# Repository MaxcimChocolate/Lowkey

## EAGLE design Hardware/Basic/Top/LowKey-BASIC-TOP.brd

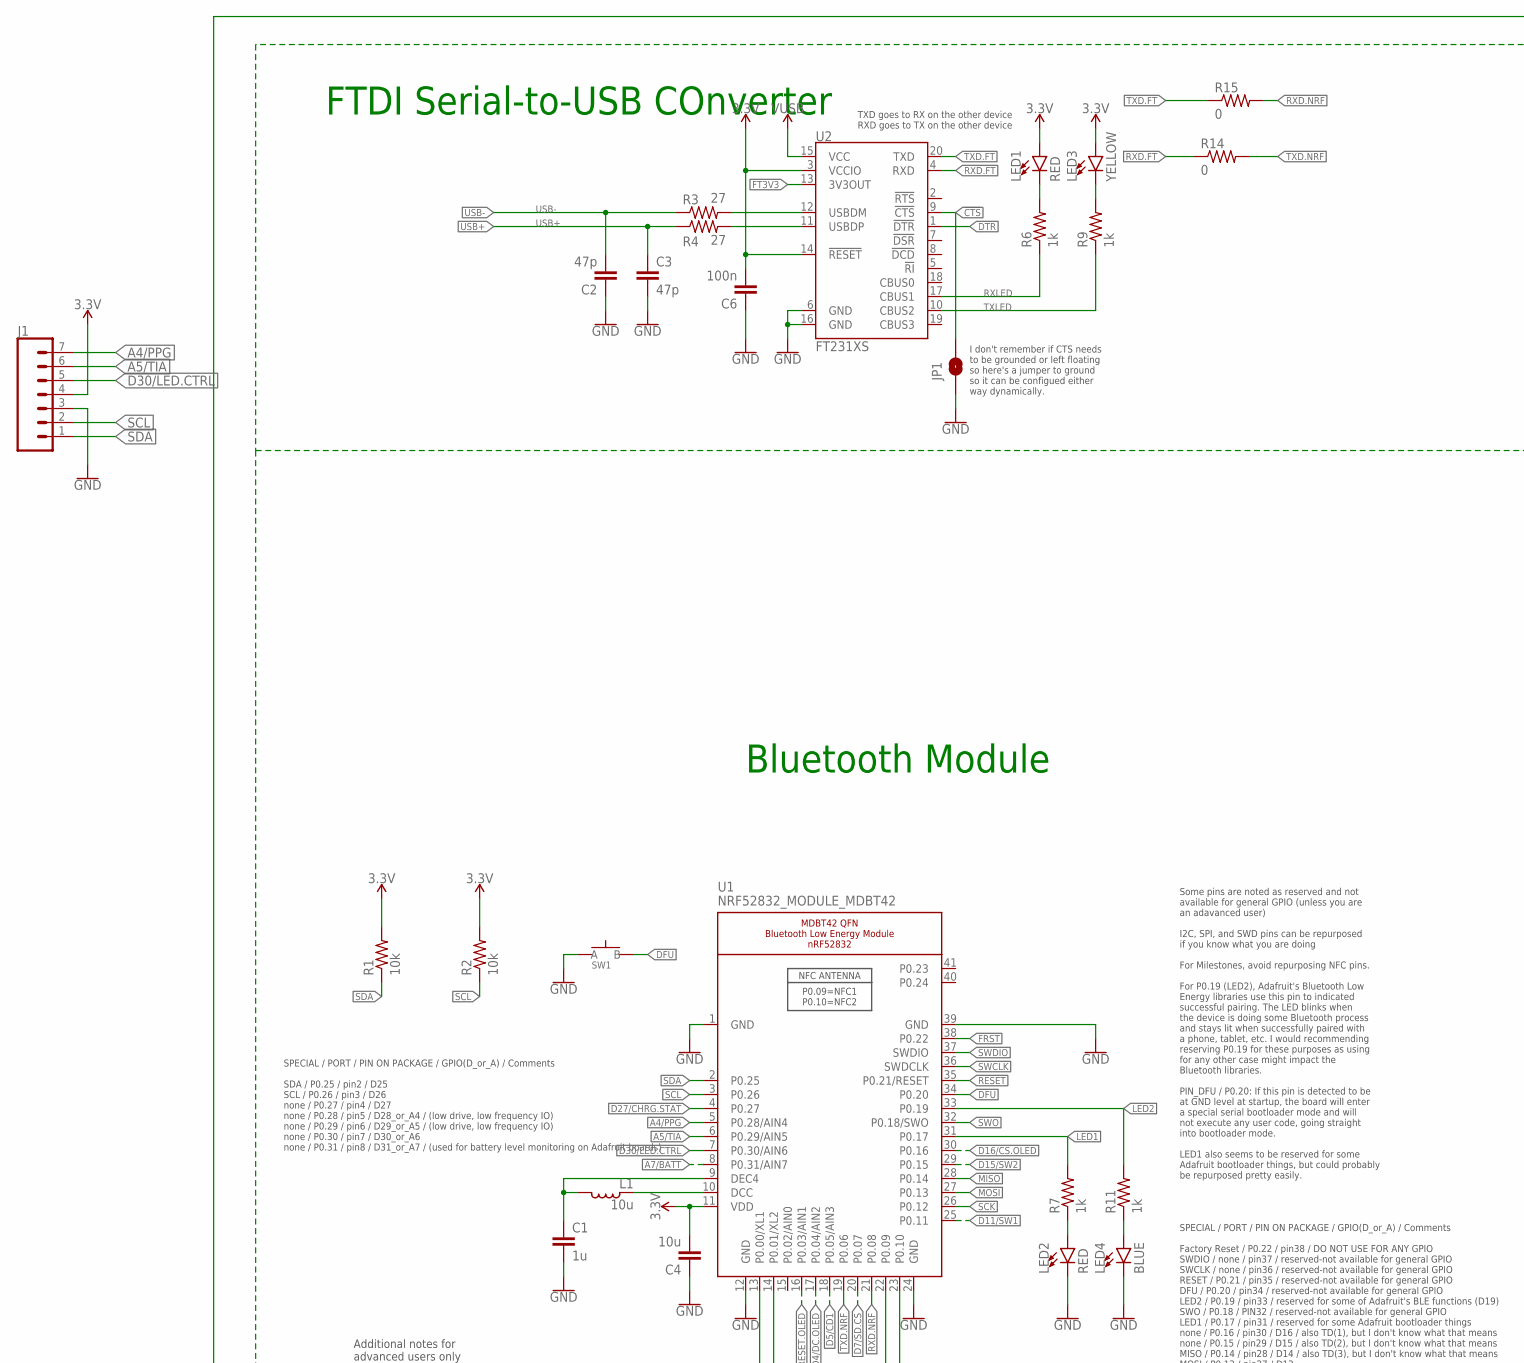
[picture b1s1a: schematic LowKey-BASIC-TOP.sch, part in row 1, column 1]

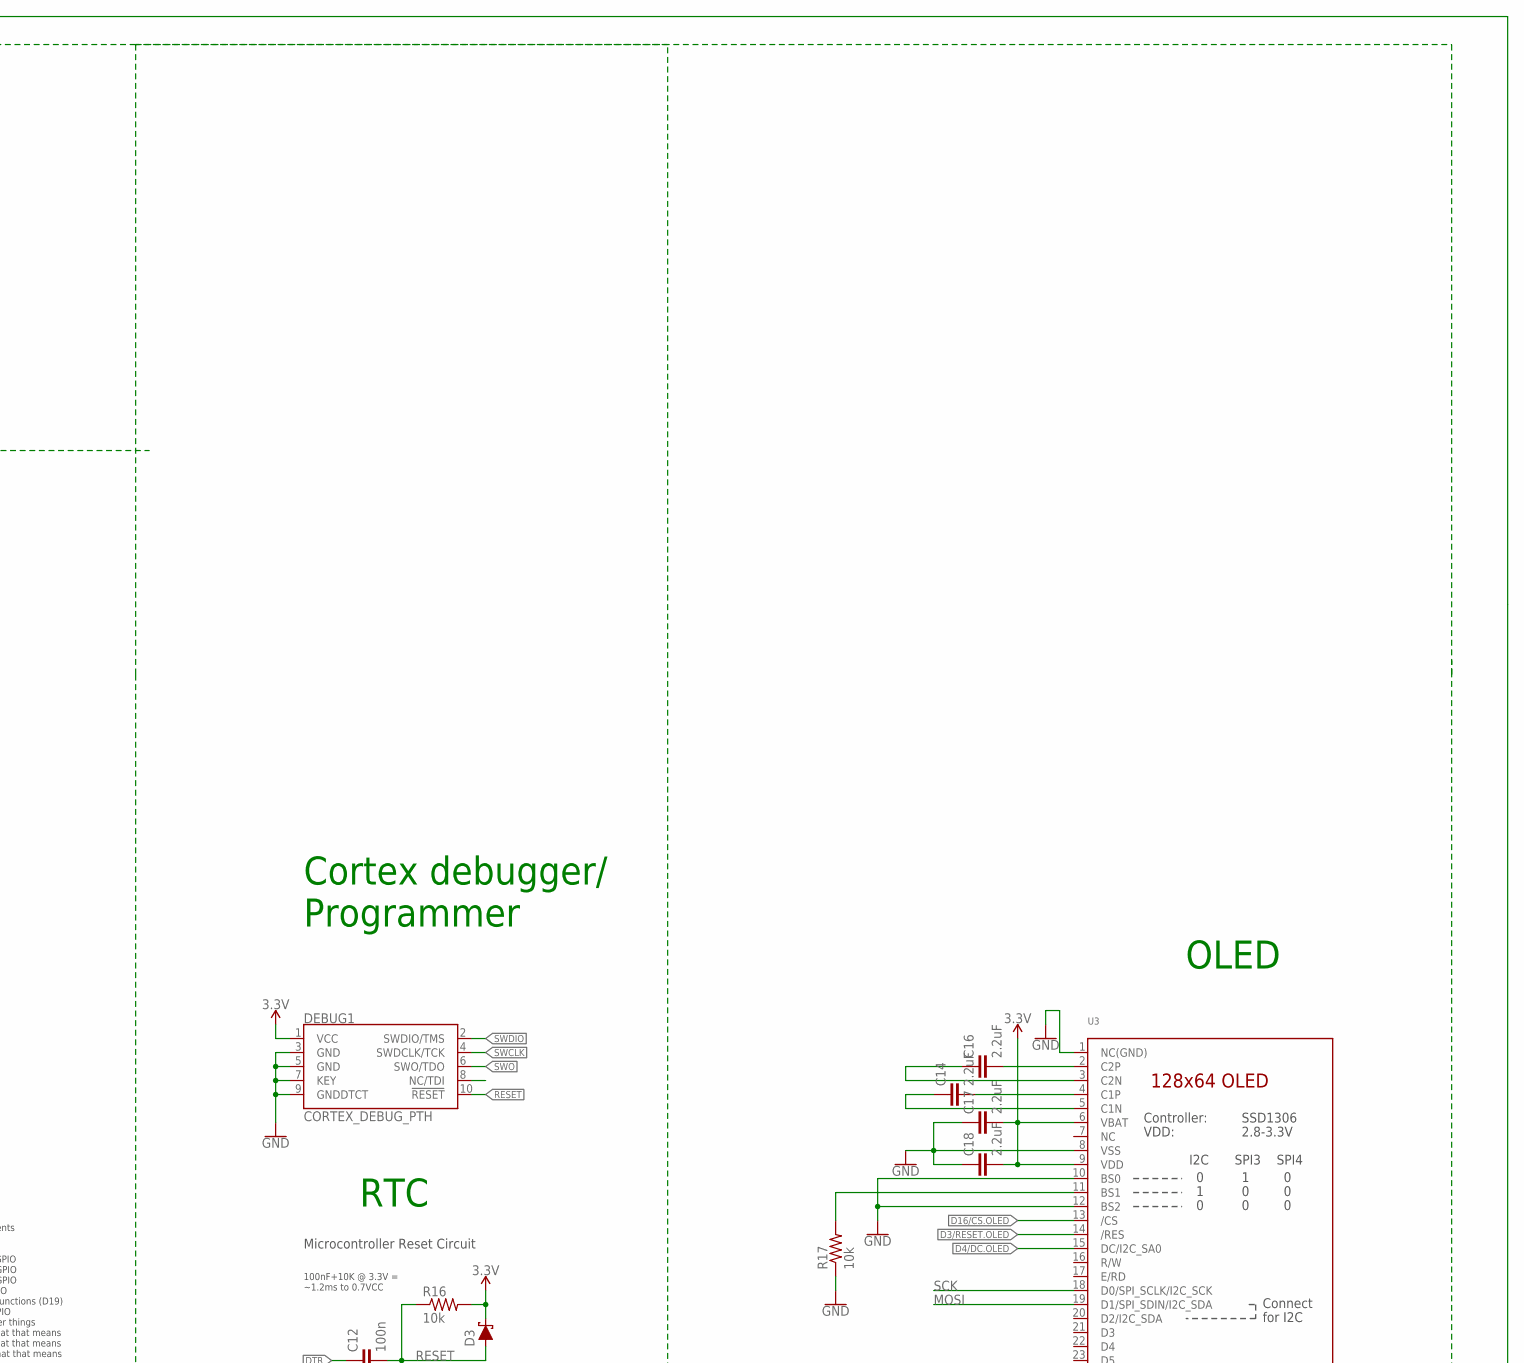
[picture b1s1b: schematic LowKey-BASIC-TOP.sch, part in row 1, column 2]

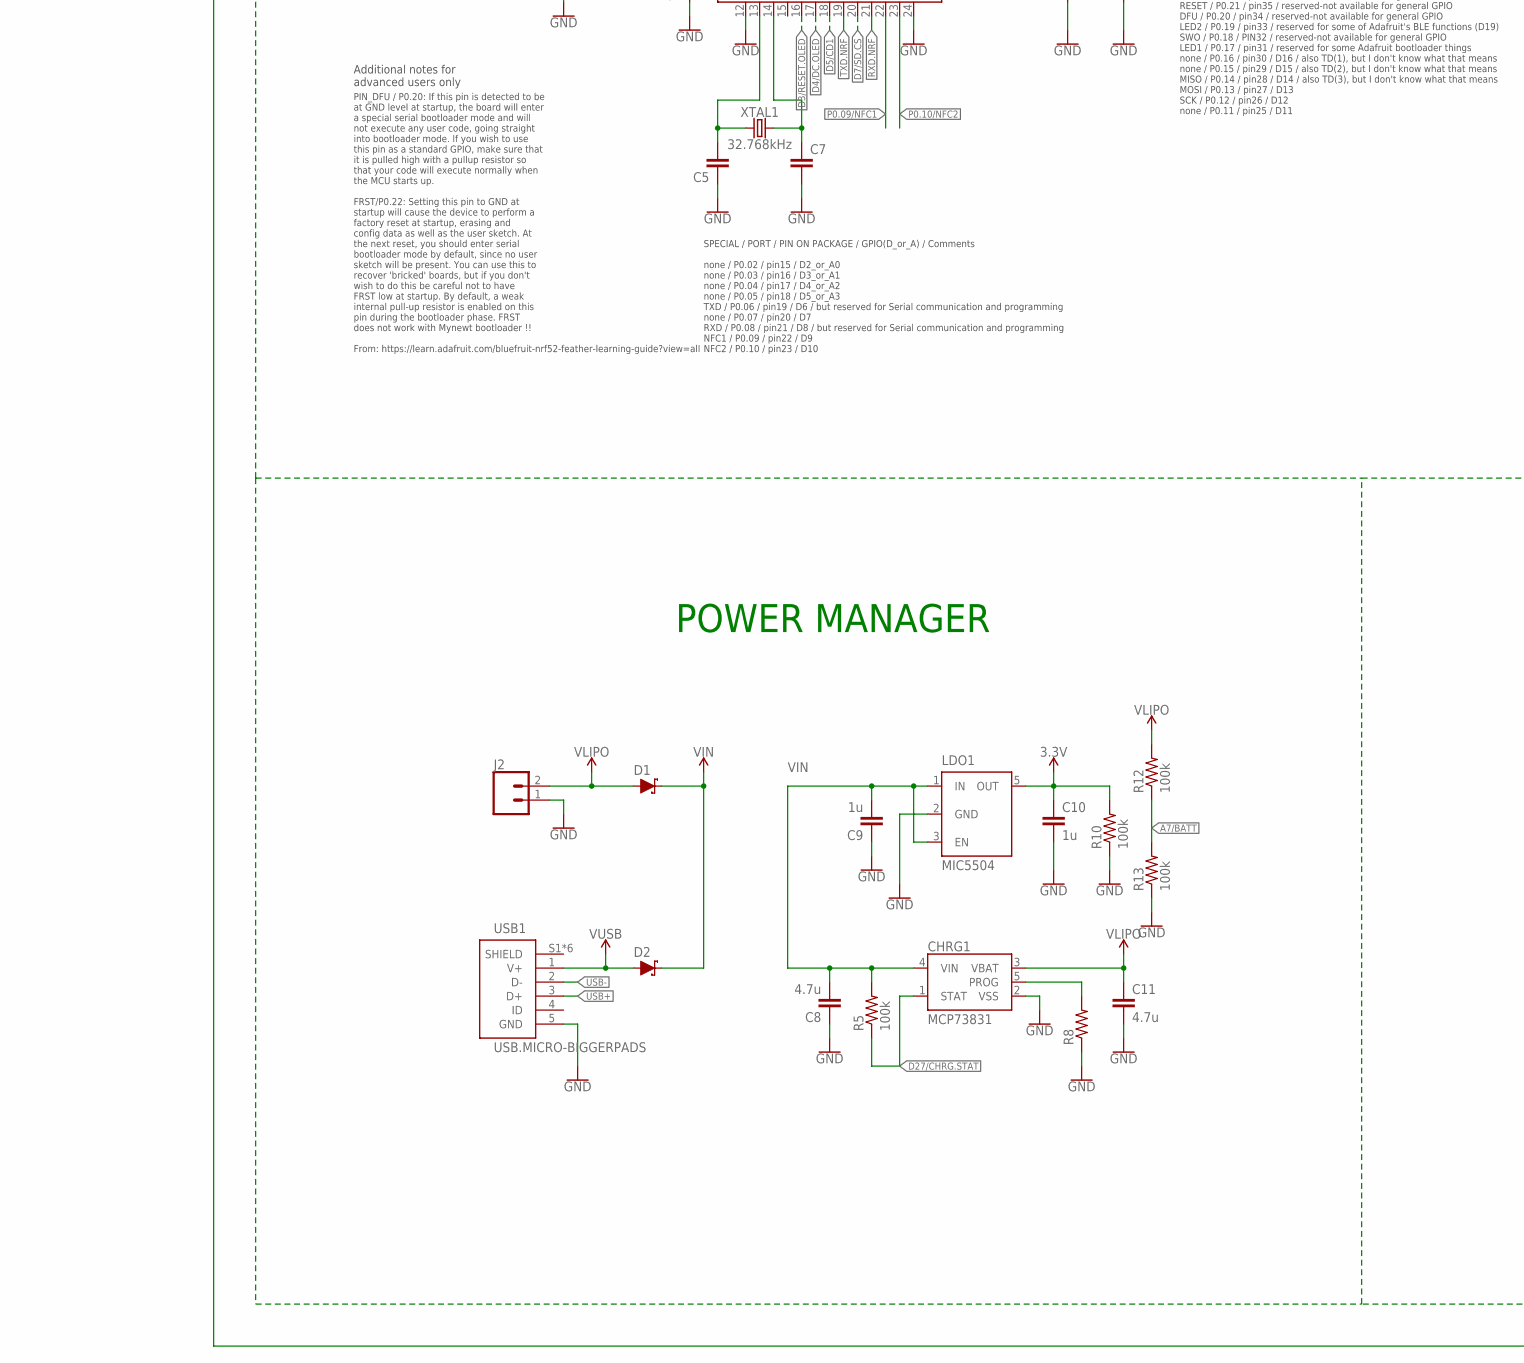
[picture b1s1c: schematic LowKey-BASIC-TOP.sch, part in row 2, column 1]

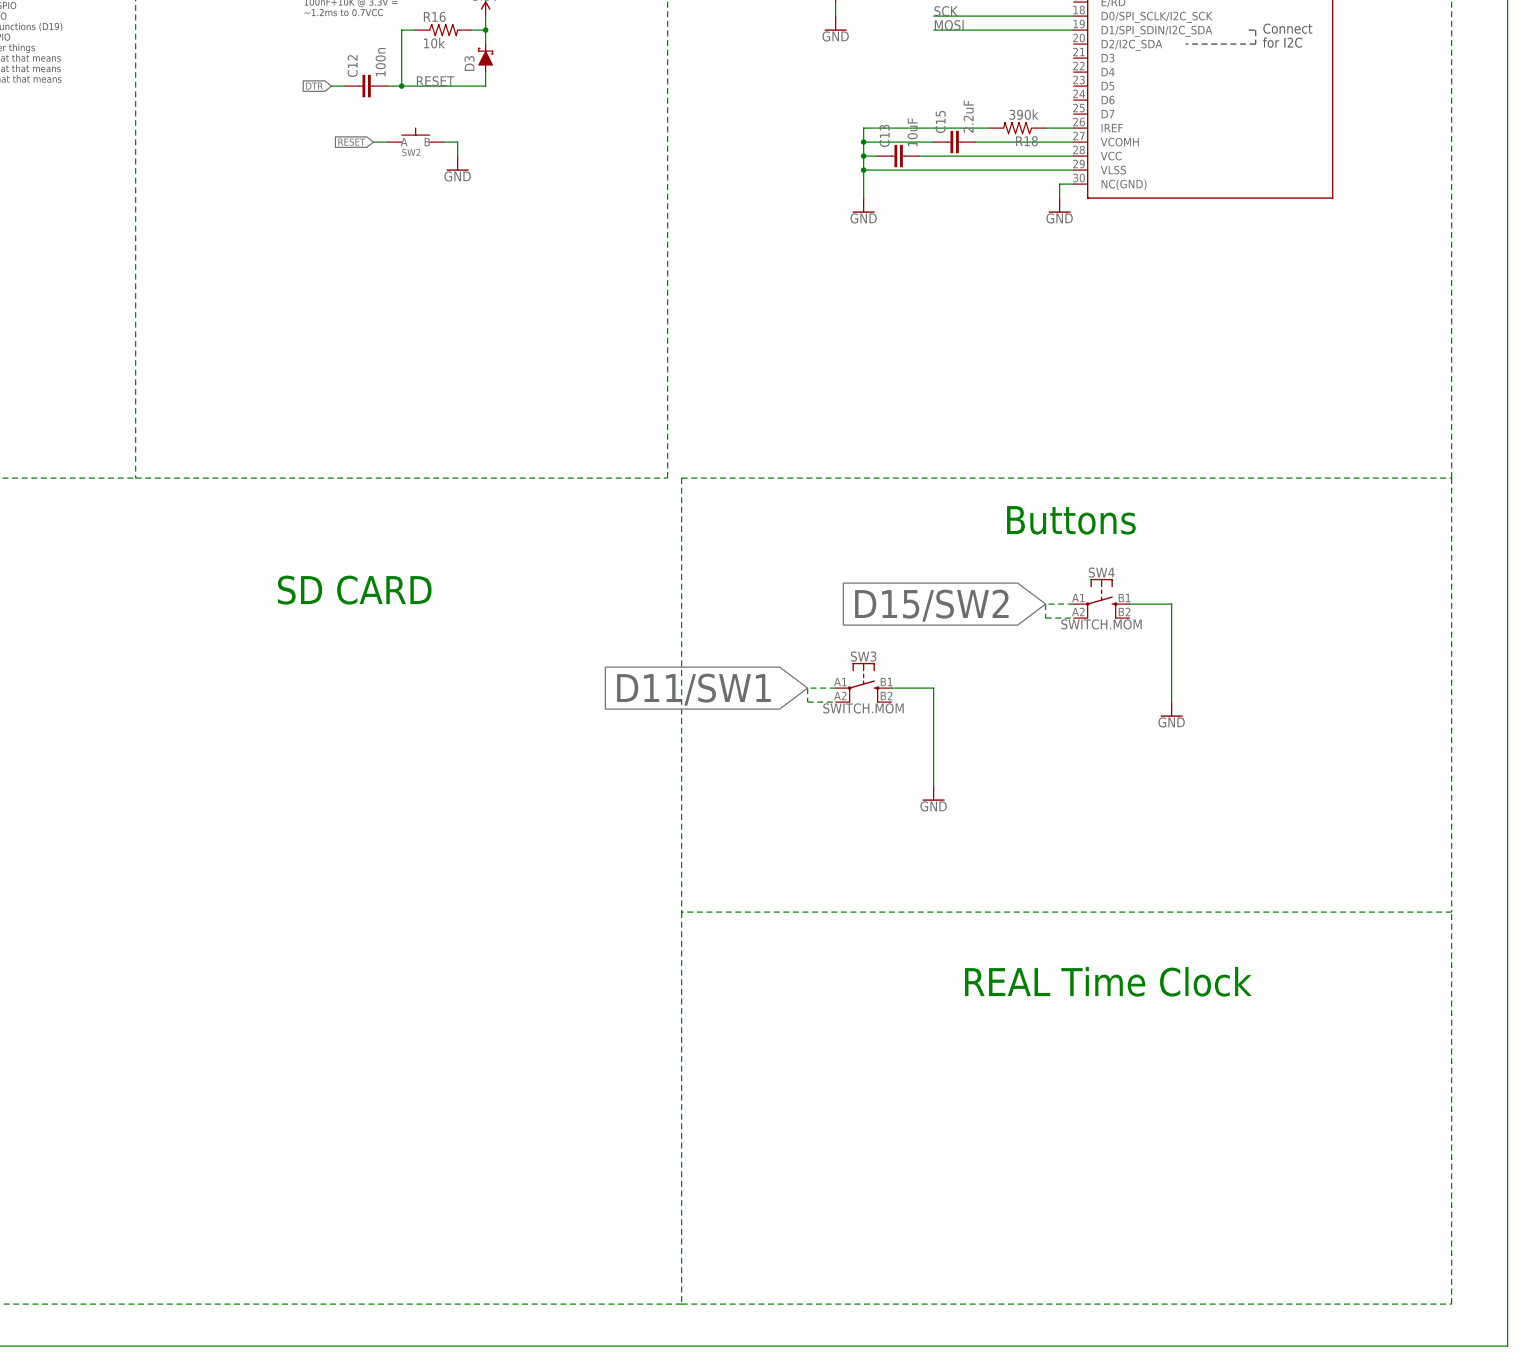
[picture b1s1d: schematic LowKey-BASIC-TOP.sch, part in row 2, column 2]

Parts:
C1, C9, C10: 1u; C0603
C2, C3: 47p; C0603
C4: 10u; C0805
C5, C7: CAPACITOR0603; C0603
C6, C12: 100n; C0603
C8, C11: 4.7u; C0603
C13: 10uF; C0603
C14, C16, C17, C18: 2.2uF; C0402
C15: 2.2uF; C0603
CHRG1: MCP73831; SOT23-5
D1, D2, D3: SCHOTTKY-USC; USC
DEBUG1: CORTEX_DEBUG_PTH; 2X5-PTH-1.27MM
J1: CONN_07-1.27MM; 1X07_1.27MM
J2: CONN_02; 1X02
JP1: JUMPER-SMT_2_NO_SILK; SMT-JUMPER_2_NO_SILK
L1: 10u; L0603
LDO1: MIC5504; SOT23-5
LED1, LED2: RED; LED-0603
LED3: YELLOW; LED-0603
LED4: BLUE; LED-0603
R1, R2, R16, R17: 10k; R0603
R3, R4: 27; R0603
R5, R10, R12, R13: 100k; R0603
R6, R7, R9, R11: 1k; R0603
R8: RESISTOR0603; R0603
R14, R15: 0; R0603
R18: 390k; R0603
SW1, SW2: SPST-PTS830GG140-COPY.1-3; BUTTON-GULLWING
SW3, SW4: SWITCH.MOM; TACTILE_SWITCH_SMD_6.2MM_TALL
U1: NRF52832_MODULE_MDBT42; BLE_MODULE_RAYTAC_MDBT42
U2: FT231XS; SSOP20_L
U3: DISP_OLED_UG-2864HSWEG01-NO-WRAPAROUND; UG-2864HSWEG01_0.96IN_NO-WRAPAROUND
USB1: USB.MICRO-BIGGERPADS; USB-MICRO-01.BIGGERPADS
XTAL1: 32.768kHz; 2-SMD.NOLEAD.2.0MMTO1.2MM

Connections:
3.3V: C4.2, C6.2, C10.1, C17.2, C18.2, D3.- (C), DEBUG1.1 (VCC), J1.4, LDO1.5 (OUT), LED1.A, LED3.A, R1.2, R2.2, R10.2, R16.2, U1.11 (VDD), U2.3 (VCCIO), U2.14 (!RESET), U3.6 (VBAT), U3.9 (VDD)
!CTS: JP1.2, U2.9 (!CTS)
A4/PPG: J1.7, U1.5 (P0.28/AIN4)
A5/TIA: J1.6, U1.6 (P0.29/AIN5)
A7/BATT: R12.1, R13.2, U1.8 (P0.31/AIN7)
D3/RESET.OLED: U1.16 (P0.03/AIN1), U3.14 (/RES)
D4/DC.OLED: U1.17 (P0.04/AIN2), U3.15 (DC/I2C_SA0)
D5/CD1: U1.18 (P0.05/AIN3)
D7/SD.CS: U1.20 (P0.07)
D11/SW1: SW3.A1 (1), SW3.A2 (2), U1.25 (P0.11)
D15/SW2: SW4.A1 (1), SW4.A2 (2), U1.29 (P0.15)
D16/CS.OLED: U1.30 (P0.16), U3.13 (/CS)
D27/CHRG.STAT: CHRG1.1 (STAT), R5.1, U1.4 (P0.27)
D30/LED.CTRL: J1.5, U1.7 (P0.30/AIN6)
DFU: SW1.3 (B), U1.34 (P0.20)
DTR: C12.1, U2.1 (!DTR)
FRST: U1.38 (P0.22)
FT3V3: U2.13 (3V3OUT)
GND: C1.2, C2.1, C3.2, C4.1, C5.1, C6.1, C7.2, C8.1, C9.1, C10.2, C11.2, C13.1, C15.1, C17.1, C18.1, CHRG1.2 (VSS), DEBUG1.3 (GND), DEBUG1.5 (GND), DEBUG1.7 (KEY), DEBUG1.9 (GNDDTCT), J1.3, J2.1, JP1.1, LDO1.2 (GND), LED2.C, LED4.C, R8.1, R10.1, R13.1, R17.1, R18.2, SW1.1 (A), SW2.3 (B), SW3.B1 (3), SW4.B1 (3), U1.1 (GND), U1.12 (GND), U1.24 (GND), U1.39 (GND), U2.6 (GND), U2.16 (GND), U3.1 (NC(GND)), U3.8 (VSS), U3.10 (BS0), U3.12 (BS2), U3.29 (VLSS), U3.30 (NC(GND)), USB1.5 (GND)
LED1: R7.2, U1.31 (P0.17)
LED2: R11.2, U1.33 (P0.19)
MISO: U1.28 (P0.14)
MOSI: U1.27 (P0.13), U3.19 (D1/SPI_SDIN/I2C_SDA)
unnamed: R17.2, U3.11 (BS1)
unnamed: R18.1, U3.26 (IREF)
unnamed: C16.2, U3.2 (C2P)
unnamed: C5.2, U1.13 (P0.00/XL1), XTAL1.P$1 (1)
unnamed: C16.1, U3.3 (C2N)
unnamed: C7.1, U1.14 (P0.01/XL2), XTAL1.P$2 (2)
unnamed: C14.2, U3.4 (C1P)
unnamed: C14.1, U3.5 (C1N)
unnamed: LED2.A, R7.1
unnamed: LED4.A, R11.1
unnamed: L1.1, U1.10 (DCC)
unnamed: C1.1, L1.2, U1.9 (DEC4)
unnamed: C13.2, U3.28 (VCC)
unnamed: C15.2, U3.27 (VCOMH)
unnamed: CHRG1.5 (PROG), R8.2
unnamed: R3.2, U2.12 (USBDM)
unnamed: R4.2, U2.11 (USBDP)
unnamed: LED1.C, R6.2
unnamed: LED3.C, R9.2
P0.09/NFC1: U1.22 (P0.09)
P0.10/NFC2: U1.23 (P0.10)
RESET: C12.2, D3.+ (A), DEBUG1.10 (!RESET), R16.1, SW2.1 (A), U1.35 (P0.21/RESET)
RXD.FT: R14.1, U2.4 (RXD)
RXD.NRF: R15.2, U1.21 (P0.08)
RXLED: R6.1, U2.17 (CBUS1)
SCK: U1.26 (P0.12), U3.18 (D0/SPI_SCLK/I2C_SCK)
SCL: J1.2, R2.1, U1.3 (P0.26)
SDA: J1.1, R1.1, U1.2 (P0.25)
SWCLK: DEBUG1.4 (SWDCLK/TCK), U1.36 (SWDCLK)
SWDIO: DEBUG1.2 (SWDIO/TMS), U1.37 (SWDIO)
SWO: DEBUG1.6 (SWO/TDO), U1.32 (P0.18/SWO)
TXD.FT: R15.1, U2.20 (TXD)
TXD.NRF: R14.2, U1.19 (P0.06)
TXLED: R9.1, U2.10 (CBUS2)
USB+: C3.1, R4.1, USB1.3 (D+)
USB-: C2.2, R3.1, USB1.2 (D-)
VIN: C8.2, C9.2, CHRG1.4 (VIN), D1.- (C), D2.- (C), LDO1.1 (IN), LDO1.3 (EN), R5.2
VLIPO: C11.1, CHRG1.3 (VBAT), D1.+ (A), J2.2, R12.2
V_USB: D2.+ (A), U2.15 (VCC), USB1.1 (V+)

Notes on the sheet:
Microcontroller Reset Circuit
100nF+10K @ 3.3V = ~1.2ms to 0.7VCC
SPECIAL / PORT / PIN ON PACKAGE / GPIO(D_or_A) / Comments SDA / P0.25 / pin2 / D25 SCL / P0.26 / pin3 / D26 none / P0.27 / pin4 / D27 none / P0.28 / pin5 / D28_or_A4 / (low drive, low frequency IO) none / P0.29 / pin6 / D29_or_A5 / (low drive, low frequency IO) none / P0.30 / pin7 / D30_or_A6 none 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
SPECIAL / PORT / PIN ON PACKAGE / GPIO(D_or_A) / Comments none / P0.02 / pin15 / D2_or_A0 none / P0.03 / pin16 / D3_or_A1 none / P0.04 / pin17 / D4_or_A2 none / P0.05 / pin18 / D5_or_A3 TXD / P0.06 / pin19 / D6 / but reserved for Serial communication and programming none / P0.07 / pin20 / D7 RXD / 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
SPECIAL / PORT / PIN ON PACKAGE / GPIO(D_or_A) / Comments Factory Reset / P0.22 / pin38 / DO NOT USE FOR ANY GPIO SWDIO / none / pin37 / reserved-not available for general GPIO SWCLK / none / pin36 / reserved-not available for general GPIO RESET / P0.21 / pin35 / reserved-not available for general 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
Some pins are noted as reserved and not available for general GPIO (unless you are an adavanced user) I2C, SPI, and SWD pins can be repurposed if you know what you are doing For Milestones, avoid repurposing NFC pins. For P0.19 (LED2), Adafruit's Bluetooth Low Energy libraries use this pin to indic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
PIN_DFU / P0.20: If this pin is detected to be at GND level at startup, the board will enter a special serial bootloader mode and will not execute any user code, going straight into bootloader mode. If you wish to use this pin as a standard GPIO, make sure that it is pulled high with a pullup resis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
Additional notes for advanced users only
OLED
POWER MANAGER
SD CARD
Buttons
REAL Time Clock
Cortex debugger/ Programmer
RTC
Bluetooth Module
TXD goes to RX on the other device RXD goes to TX on the other device
I don't remember if CTS needs to be grounded or left floating so here's a jumper to ground so it can be configued either way dynamically.
FTDI Serial-to-USB COnverter

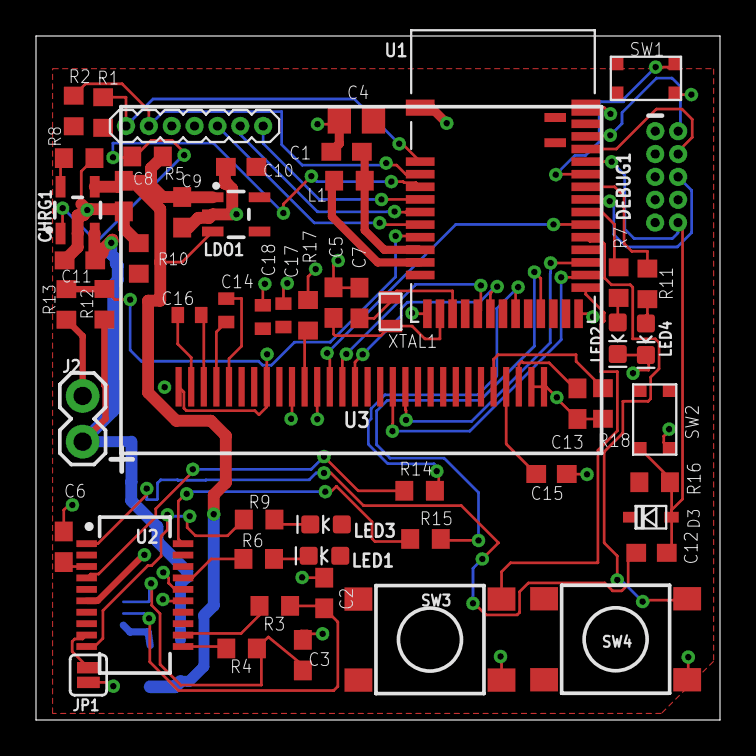
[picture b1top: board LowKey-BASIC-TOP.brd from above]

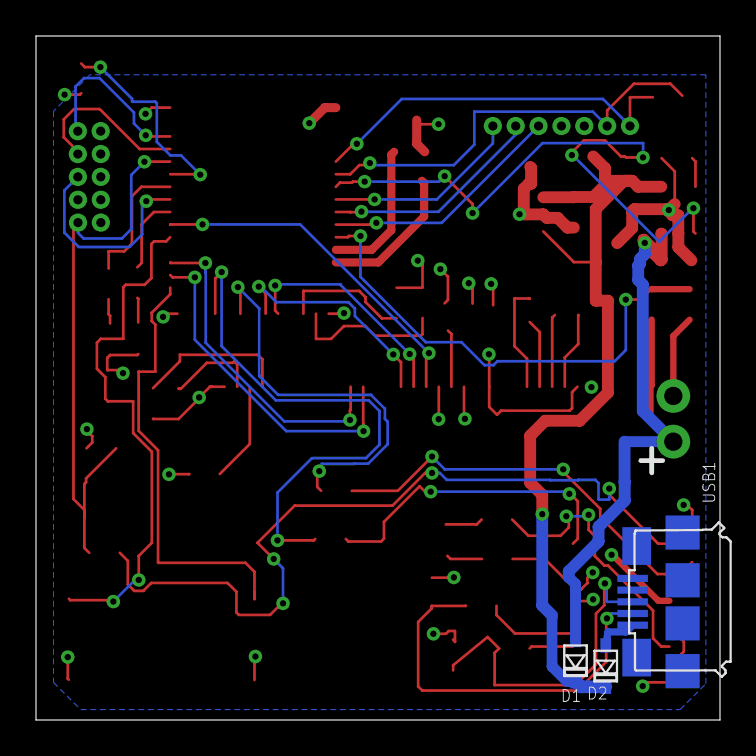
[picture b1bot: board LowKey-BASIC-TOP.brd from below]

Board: 2 copper layers, 38.0 x 38.0 mm, 59 parts (3 on the bottom side), 55 nets.

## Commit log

2020-06-30 Features List
2020-07-01 Organized Repo
2020-07-07 Recreated .txt file
2020-07-08 Added basic top board elements
2020-07-09 Top connections
2020-07-13 Take 4 Routing Top Board 17 min
2020-07-14 Take 4 Complete
2020-07-14 added arduino project
2020-07-14 Copied PPG and Bottom Boards in
2020-07-14 Fixed deleted files
2020-07-28 Take 06
2020-07-28 Take 7
2020-07-29 Finished routing top board
